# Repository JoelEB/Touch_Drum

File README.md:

# Touch_Drum
A repo for all thing TouchDrum Related: hardware/software files, 3D files, etc.

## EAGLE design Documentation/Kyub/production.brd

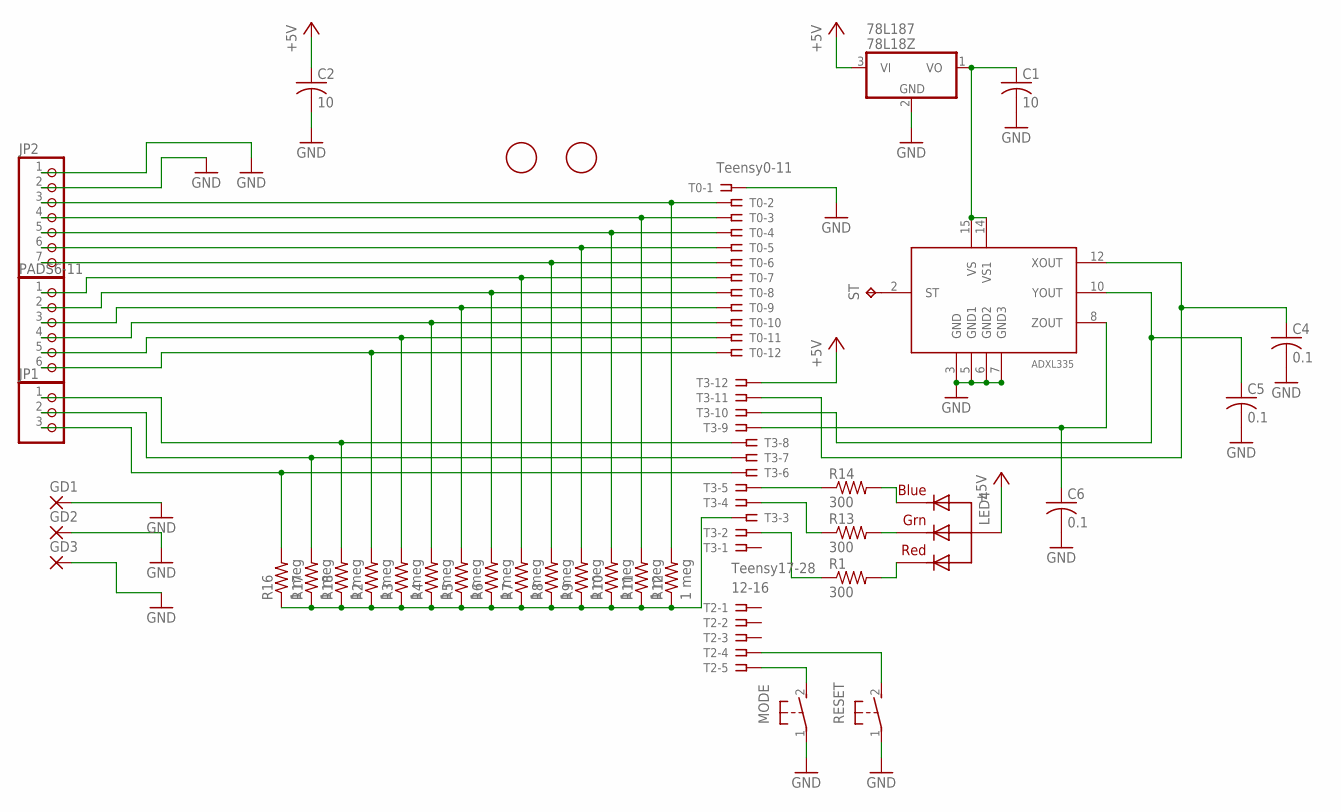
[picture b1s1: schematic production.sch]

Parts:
78L187: 78L18Z; TO92
ADXL335: ADXL33X; 16LCSP
C1, C2: 10; C050-024X044
C4, C5, C6: 0.1; C050-024X044
FID1, FID2: FIDUCIAL; FIDUCIAL_1MM
GD1, GD2, GD3: 3,17/1,1
JP1: PINHD-1X3; 1X03
JP2: PINHD-1X7; 1X07
LED4: RGBLED_CA-5MM; LED5MMRGB
MODE: 31-XX; B3F-31XX
PADS6-11: PINHD-1X6; 1X06
R1, R13, R14: 300; 0207/2V
R2, R3, R4, R5, R6, R7, R8, R9, R10, R11, R12, R16, R17, R18: 1 meg; 0207/2V
RESET: 31-XX; B3F-31XX
ST: TPTP17R; TP17R
T0: Teensy0-11; SSW-112-02-S-S
T2: 12-16; SSW-105-02-S-S
T3: Teensy17-28; SSW-112-02-S-S

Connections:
+5V: 78L187.3 (VI), C2.1, LED4.2 (VCC), T3.12
GND: 78L187.2 (GND), ADXL335.3 (GND), ADXL335.5 (GND1), ADXL335.6 (GND2), ADXL335.7 (GND3), C1.2, C2.2, C4.2, C5.2, C6.2, GD1.1, GD2.1, GD3.1, JP2.1, JP2.2, MODE.1, RESET.1, T0.1
unnamed: JP2.3, R12.2, T0.2
unnamed: JP2.4, R11.2, T0.3
unnamed: PADS6-11.1, R7.2, T0.7
unnamed: PADS6-11.2, R6.2, T0.8
unnamed: PADS6-11.3, R5.2, T0.9
unnamed: PADS6-11.4, R4.2, T0.10
unnamed: PADS6-11.5, R3.2, T0.11
unnamed: R14.1, T3.5
unnamed: JP2.6, R9.2, T0.5
unnamed: JP2.5, R10.2, T0.4
unnamed: ADXL335.12 (XOUT), C4.1, T3.11
unnamed: PADS6-11.6, R2.2, T0.12
unnamed: LED4.4 (BLUE), R14.2
unnamed: ADXL335.2 (ST), ST.TP
unnamed: ADXL335.8 (ZOUT), C6.1, T3.9
unnamed: LED4.3 (GREEN), R13.2
unnamed: JP1.3, R16.2, T3.6
unnamed: JP1.2, R17.2, T3.7
unnamed: JP1.1, R18.2, T3.8
unnamed: R2.1, R3.1, R4.1, R5.1, R6.1, R7.1, R8.1, R9.1, R10.1, R11.1, R12.1, R16.1, R17.1, R18.1, T3.3
unnamed: R13.1, T3.4
unnamed: R1.1, T3.2
unnamed: JP2.7, R8.2, T0.6
unnamed: LED4.1 (RED), R1.2
unnamed: ADXL335.10 (YOUT), C5.1, T3.10
unnamed: MODE.2 (S), T2.5
unnamed: RESET.2 (S), T2.4
VS1: 78L187.1 (VO), ADXL335.14 (VS1), ADXL335.15 (VS), C1.1

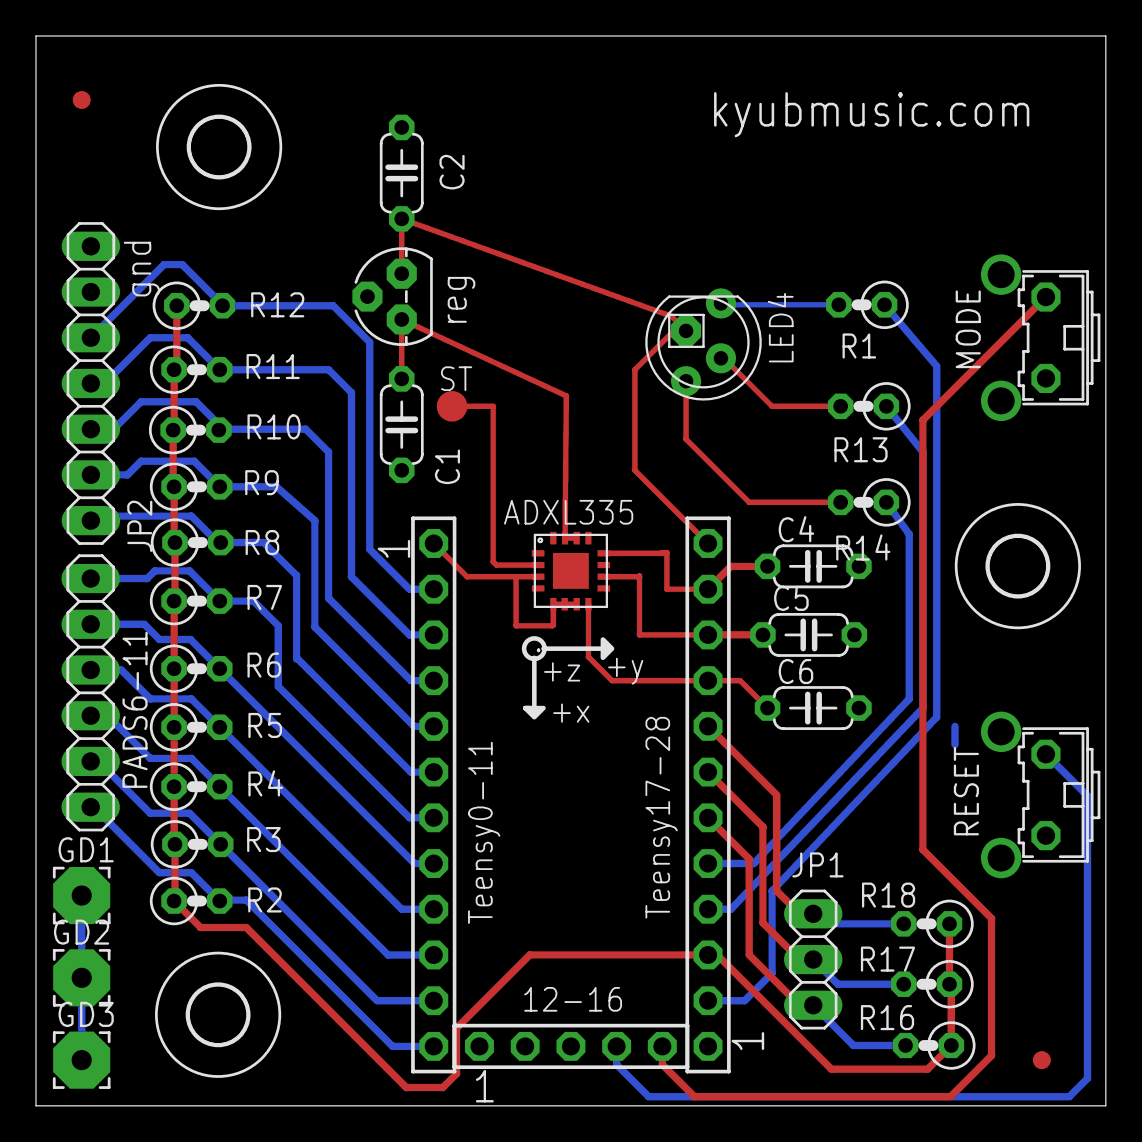
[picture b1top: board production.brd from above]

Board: 2 copper layers, 59.4 x 59.4 mm, 42 parts (0 on the bottom side), 30 nets.

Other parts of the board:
U$3, U$4, U$5: 1/8 hole for M3 screw; 3,2

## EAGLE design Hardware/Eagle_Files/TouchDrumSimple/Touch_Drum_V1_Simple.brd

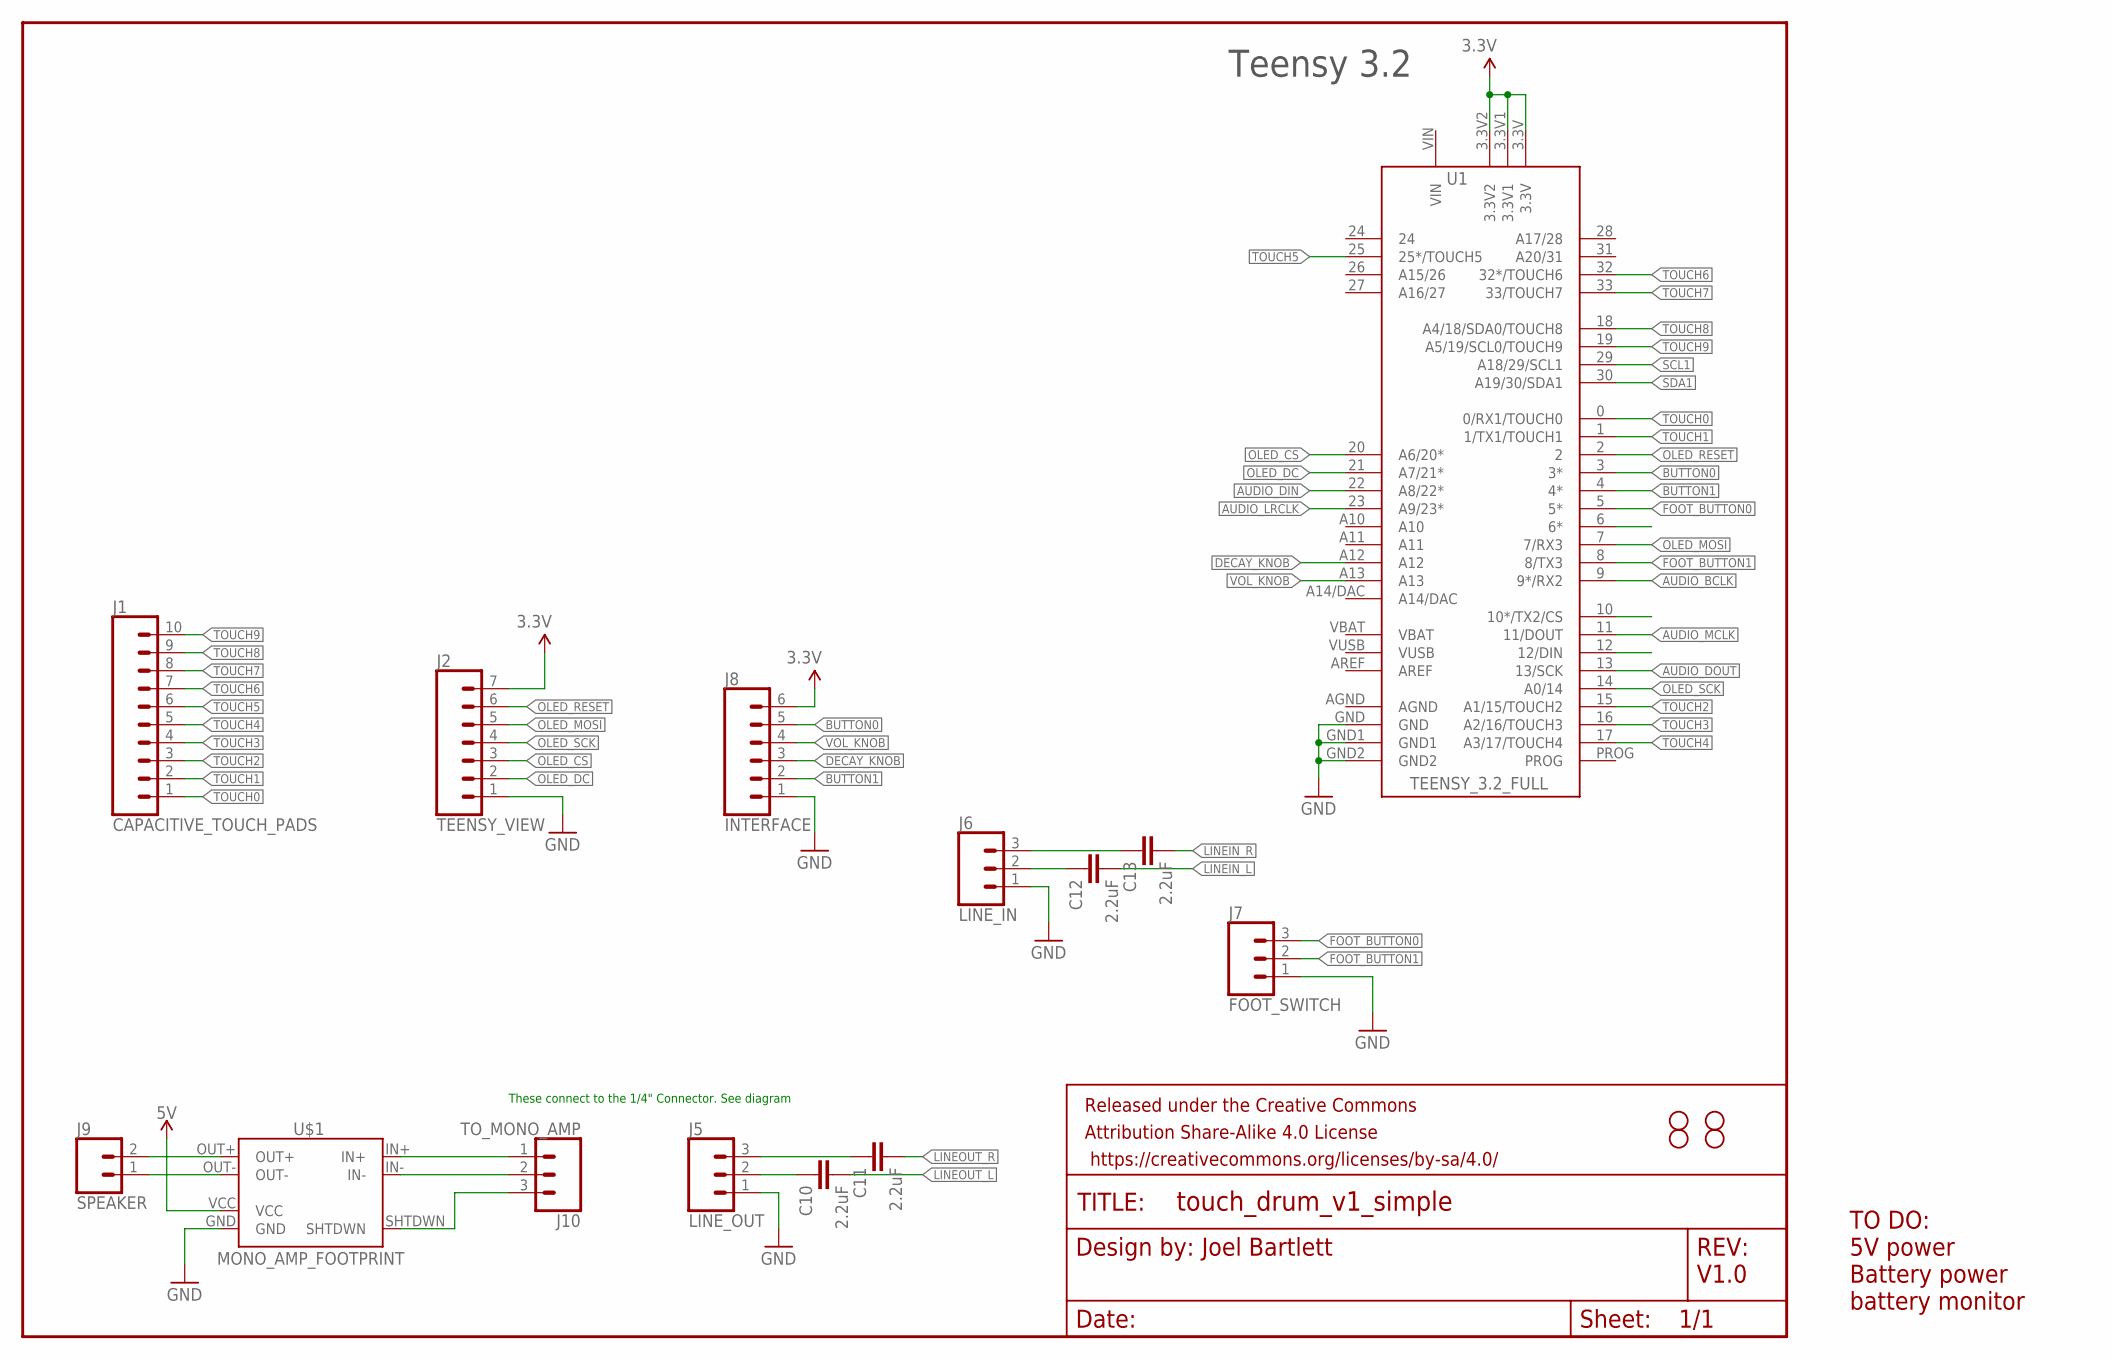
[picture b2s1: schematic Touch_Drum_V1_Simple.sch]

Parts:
C10, C11, C12, C13: 2.2uF; 0603
FRAME1: FRAME-LETTER; CREATIVE_COMMONS
H1, H2, H3, H4: STAND-OFF
J1: CAPACITIVE_TOUCH_PADS; 1X10_NO_SILK
J2: TEENSY_VIEW; 1X07_NO_SILK
J5: LINE_OUT; 1X03
J6: LINE_IN; 1X03
J7: FOOT_SWITCH; 1X03
J8: INTERFACE; 1X06
J9: SPEAKER; 1X02
J10: TO_MONO_AMP; 1X03
U1: TEENSY_3.2_FULL
U$1: MONO_AMP_FOOTPRINT

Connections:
3.3V: J2.7, J8.6, U1.3.3V, U1.3.3V1, U1.3.3V2
5V: U$1.VCC
AUDIO_BCLK: U1.9 (9*/RX2)
AUDIO_DIN: U1.22 (A8/22*)
AUDIO_DOUT: U1.13 (13/SCK)
AUDIO_LRCLK: U1.23 (A9/23*)
AUDIO_MCLK: U1.11 (11/DOUT)
BUTTON0: J8.5, U1.3 (3*)
BUTTON1: J8.2, U1.4 (4*)
DECAY_KNOB: J8.3, U1.A12
FOOT_BUTTON0: J7.3, U1.5 (5*)
FOOT_BUTTON1: J7.2, U1.8 (8/TX3)
GND: J2.1, J5.1, J6.1, J7.1, J8.1, U1.GND, U1.GND1, U1.GND2, U$1.GND
LINEIN_L: C12.2
LINEIN_R: C13.2
LINEOUT_L: C10.2
LINEOUT_R: C11.2
unnamed: J10.1, U$1.IN+
unnamed: C11.1, J5.3
unnamed: C10.1, J5.2
unnamed: C13.1, J6.3
unnamed: C12.1, J6.2
unnamed: J10.2, U$1.IN-
unnamed: J10.3, U$1.SHTDWN
OLED_CS: J2.3, U1.20 (A6/20*)
OLED_DC: J2.2, U1.21 (A7/21*)
OLED_MOSI: J2.5, U1.7 (7/RX3)
OLED_RESET: J2.6, U1.2
OLED_SCK: J2.4, U1.14 (A0/14)
OUT+: J9.2, U$1.OUT+
OUT-: J9.1, U$1.OUT-
SCL1: U1.29 (A18/29/SCL1)
SDA1: U1.30 (A19/30/SDA1)
TOUCH0: J1.1, U1.0 (0/RX1/TOUCH0)
TOUCH1: J1.2, U1.1 (1/TX1/TOUCH1)
TOUCH2: J1.3, U1.15 (A1/15/TOUCH2)
TOUCH3: J1.4, U1.16 (A2/16/TOUCH3)
TOUCH4: J1.5, U1.17 (A3/17/TOUCH4)
TOUCH5: J1.6, U1.25 (25*/TOUCH5)
TOUCH6: J1.7, U1.32 (32*/TOUCH6)
TOUCH7: J1.8, U1.33 (33/TOUCH7)
TOUCH8: J1.9, U1.18 (A4/18/SDA0/TOUCH8)
TOUCH9: J1.10, U1.19 (A5/19/SCL0/TOUCH9)
VOL_KNOB: J8.4, U1.A13

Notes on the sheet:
Teensy 3.2
Joel Bartlett
V1.0
TO DO: 5V power Battery power battery monitor
These connect to the 1/4" Connector. See diagram

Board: 2 copper layers, 19 parts (0 on the bottom side), 32 nets, no tracks yet.

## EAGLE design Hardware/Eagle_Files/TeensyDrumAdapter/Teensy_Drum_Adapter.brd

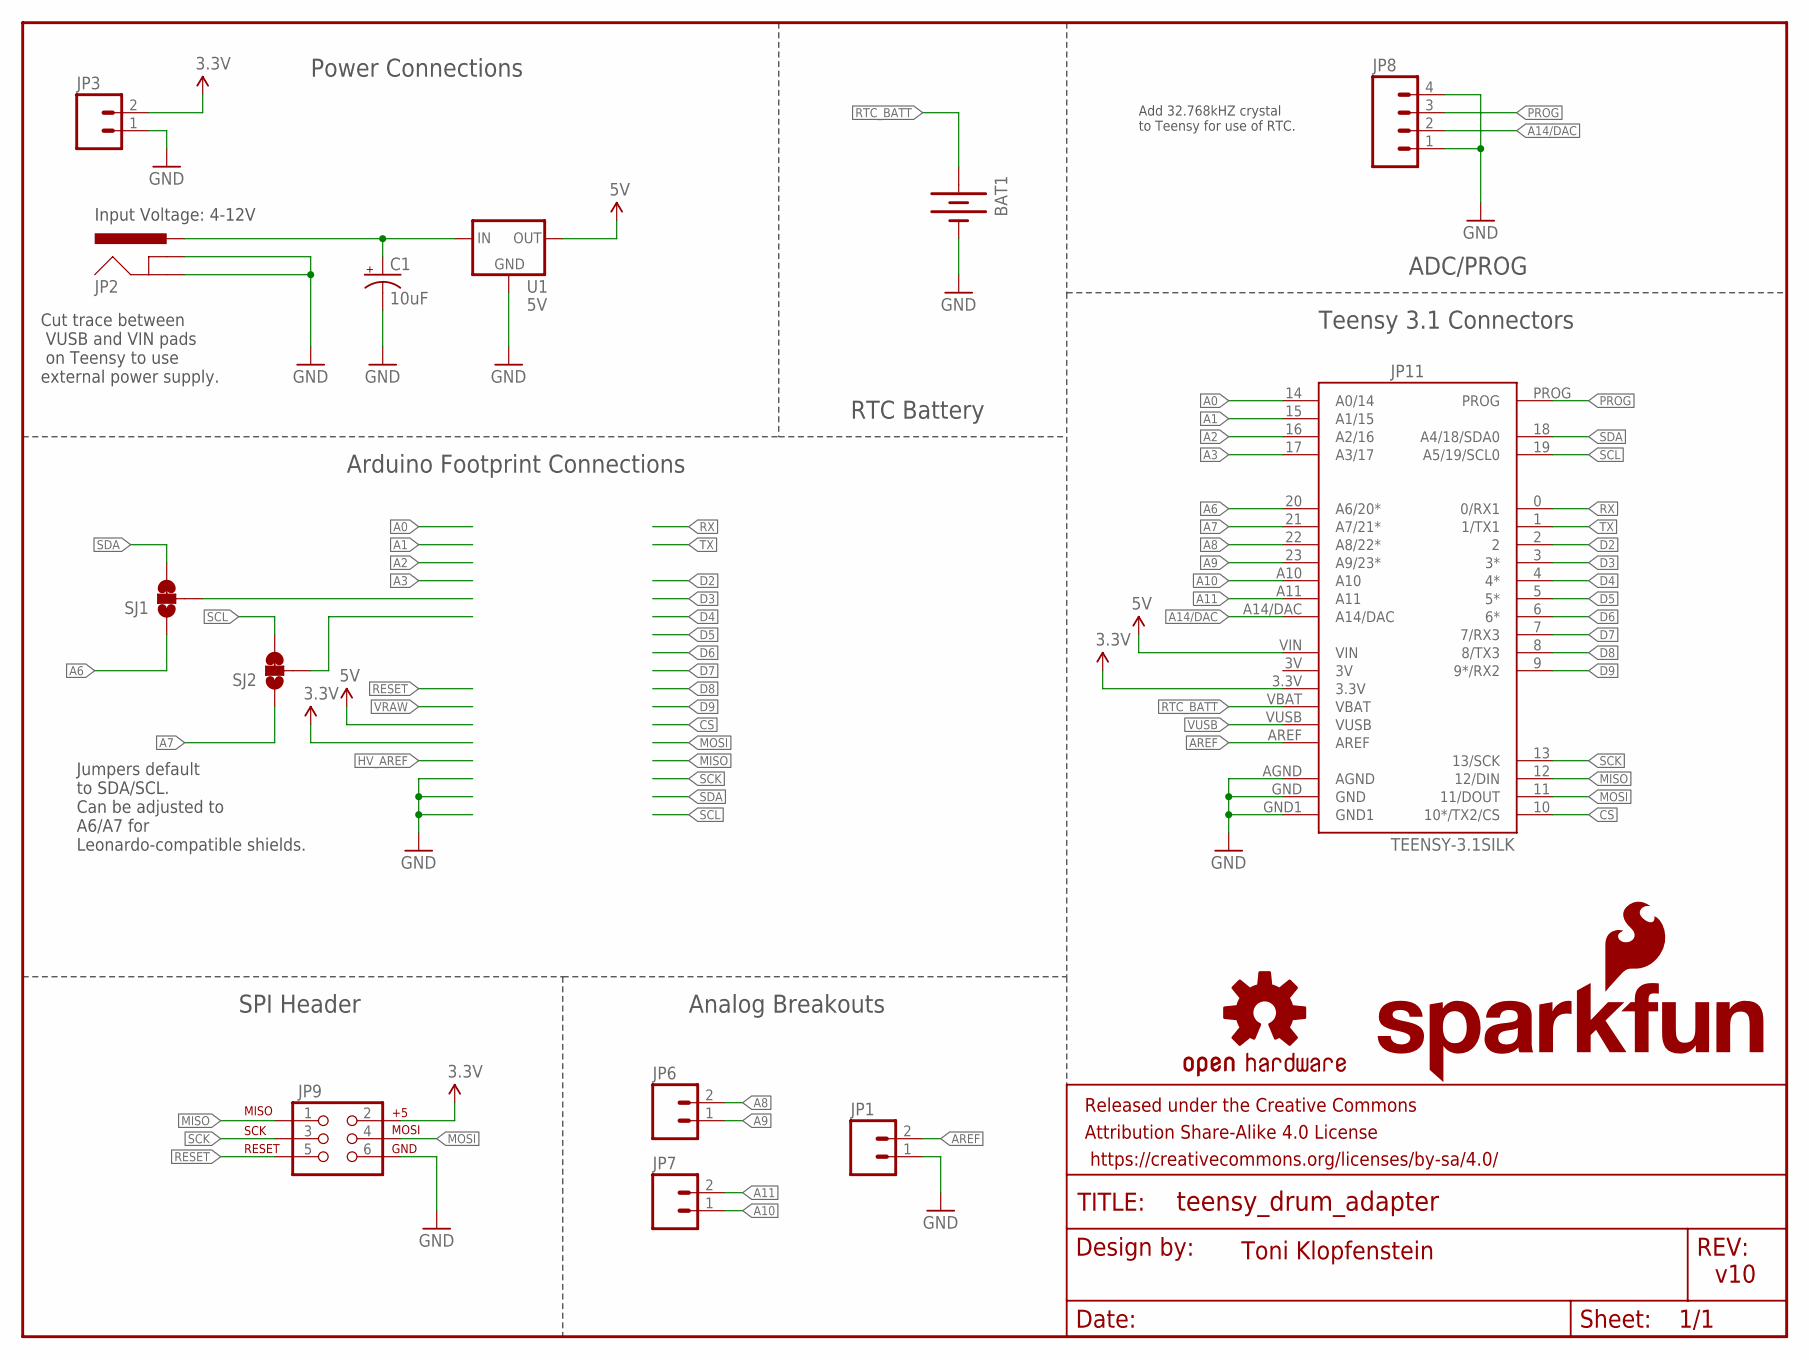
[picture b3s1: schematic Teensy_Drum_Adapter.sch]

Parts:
BAT1: BATTERY12PTH; BATTCON_12MM_PTH
C1: 10uF; CPOL-RADIAL-10UF-25V
FRAME1: FRAME-LETTER; CREATIVE_COMMONS
JP1, JP6, JP7: M02PTH; 1X02
JP2: POWER_JACKPTH_LOCK; POWER_JACK_PTH_LOCK
JP3: M02JST-PTH-2; JST-2-PTH
JP8: M04PTH; 1X04
JP9: AVR_SPI_PRG_6PTH; 2X3
JP11: TEENSY-3.1SILK; TEENSY-3.1
LOGO1: SFE_LOGO_NAME_FLAME.1_INCH; SFE_LOGO_NAME_FLAME_.1
LOGO2: OSHW-LOGOM; OSHW-LOGO-M
SJ1, SJ2: JUMPER-PAD-3-2OF3_NC_BY_TRACE_SMALL; PAD-JUMPER-3-2OF3_NC_BY_TRACE_YES_SILK_FULL_BOX
U1: 5V; TO-220-ALT

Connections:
3.3V: JP3.2, JP9.2, JP11.3.3V
5V: JP11.VIN, U1.OUT
A0: JP11.14 (A0/14)
A1: JP11.15 (A1/15)
A2: JP11.16 (A2/16)
A3: JP11.17 (A3/17)
A4: SJ1.2
A5: SJ2.2
A6: JP11.20 (A6/20*), SJ1.1
A7: JP11.21 (A7/21*), SJ2.1
A8: JP6.2, JP11.22 (A8/22*)
A9: JP6.1, JP11.23 (A9/23*)
A10: JP7.1, JP11.A10
A11: JP7.2, JP11.A11
A14/DAC: JP8.2, JP11.A14/DAC
AREF: JP1.2, JP11.AREF
CS: JP11.10 (10*/TX2/CS)
D2: JP11.2
D3: JP11.3 (3*)
D4: JP11.4 (4*)
D5: JP11.5 (5*)
D6: JP11.6 (6*)
D7: JP11.7 (7/RX3)
D8: JP11.8 (8/TX3)
D9: JP11.9 (9*/RX2)
GND: BAT1.GND (-), C1.2 (-), JP1.1, JP2.GND, JP2.GNDBREAK, JP3.1, JP8.1, JP8.4, JP9.6, JP11.AGND, JP11.GND, JP11.GND1, U1.GND
MISO: JP9.1, JP11.12 (12/DIN)
MOSI: JP9.4, JP11.11 (11/DOUT)
PROG: JP8.3, JP11.PROG
RESET: JP9.5
RTC_BATT: BAT1.VCC@1 (+), JP11.VBAT
RX: JP11.0 (0/RX1)
SCK: JP9.3, JP11.13 (13/SCK)
SCL: JP11.19 (A5/19/SCL0), SJ2.3
SDA: JP11.18 (A4/18/SDA0), SJ1.3
TX: JP11.1 (1/TX1)
VRAW: C1.1 (+), JP2.PWR, U1.IN
VUSB: JP11.VUSB

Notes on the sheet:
Input Voltage: 4-12V
Add 32.768kHZ crystal to Teensy for use of RTC.
Cut trace between VUSB and VIN pads on Teensy to use external power supply.
Jumpers default to SDA/SCL. Can be adjusted to A6/A7 for Leonardo-compatible shields.
Power Connections
Arduino Footprint Connections
SPI Header
Analog Breakouts
Teensy 3.1 Connectors
ADC/PROG
RTC Battery
v10
Toni Klopfenstein

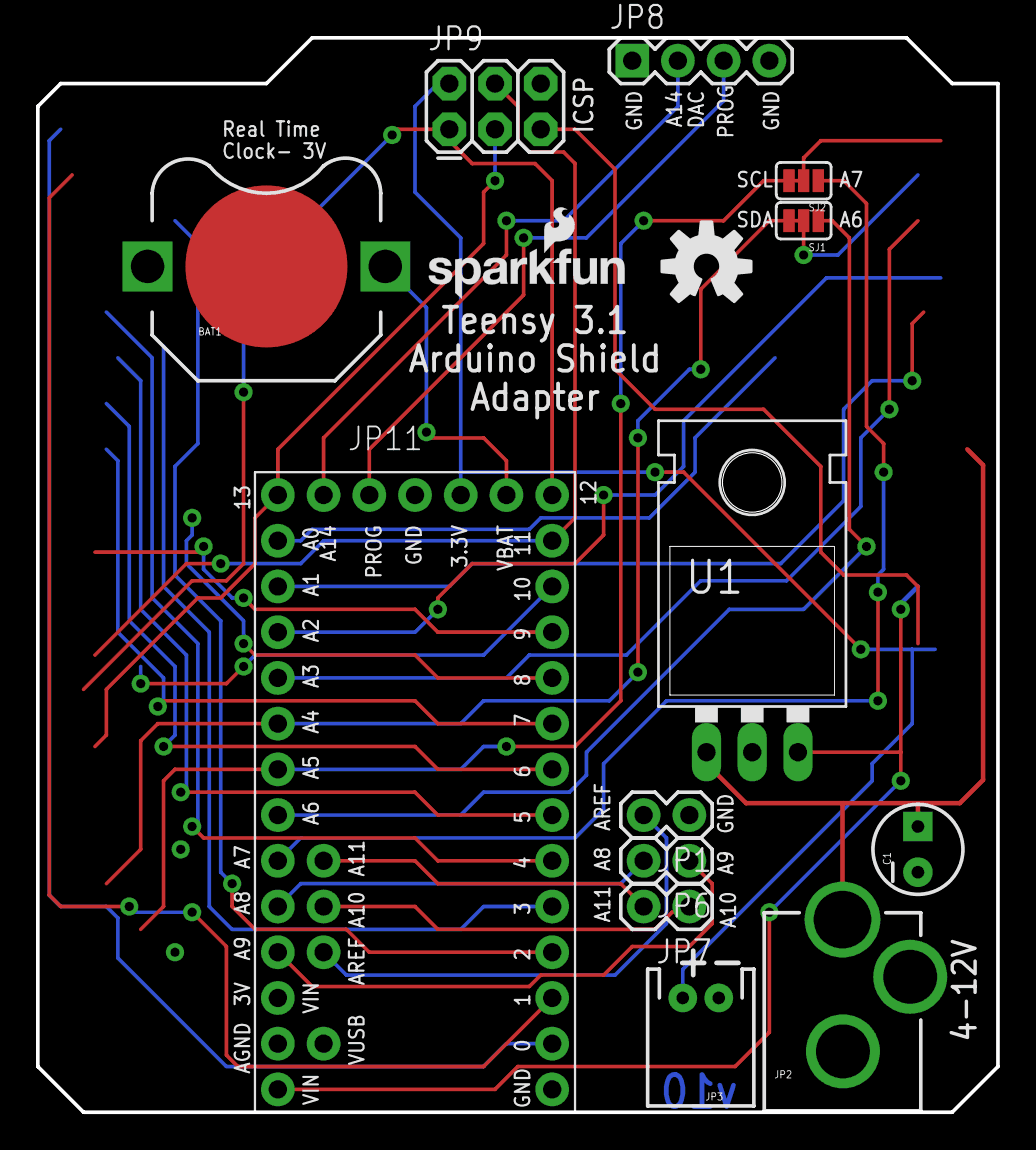
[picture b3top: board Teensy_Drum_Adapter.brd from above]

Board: 2 copper layers, 53.3 x 59.7 mm, 16 parts (0 on the bottom side), 19 nets.

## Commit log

2018-09-21 Adding website files
2018-09-21 Adding Millable PCB
2018-09-21 Updating Millable Version
2018-09-21 Update gitignore to include DRL files for gerbers
2018-09-21 Adding DRL
2018-09-24 Adding code for milled prototype
2018-09-25 Beginning Full Layout
2018-10-02 Adding functional code with Toudh Drum splash screen for all versions
2018-10-06 Adding V5 firmware
    V5 includes: MIDI, MIDI scales, overhaul of the touchRead function into one 'for loop(), adding debounce for capTouchRead buttons. Also adding lots of support files from Marshall's repository.
2018-10-06 Starting cleanup, adding master file for tupperware proto
2018-10-12 Adding Master firmware for each model
2018-10-13 Integrating multple wavefrom code with both masters
2018-10-14 Adding nRF52 BLE to Serial code
    Adding nRF52 BLE to Serial code. This was testing with the Oval app connected to the nRF52 over BLE and the nRF52 connected to a serial terminal on mac with an FTDI basic.
2018-10-25 Adding 3D and BLE files
2018-11-14 Adding a few more 3D files
2018-12-07 Mostly complete Top layer PCB of V1 Touch Drum
2018-12-20 Adding more logos
2019-08-13 Adding more reference files

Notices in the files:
parts and their libraries:
SparkFun-Aesthetics: Licensing: Creative Commons ShareAlike 4.0 International - https://creativecommons.org/licenses/by-sa/4.0
SparkFun-Aesthetics: Released under the Creative Commons Attribution Share-Alike 4.0 License
SparkFun-Aesthetics: https://creativecommons.org/licenses/by-sa/4.0
